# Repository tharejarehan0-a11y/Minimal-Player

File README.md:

# Minimal Player

**All the recordings are in JOURNAL.MD**

Minimal player is a device i can use to listen music in a compact way with only wired earphones offline and without worrying too much about the battery as it has a long battery life

---

## Why I Created This

The inspiration was from the need of having something i can carry everyday with me and listen music from with looking asthetic at the same times and some device with which i can use my wired earphones. But the thing is that i like to use such a device that gives only audio output through the audio jack bcz when you unplug it . It suddenly starts to play and doesnt stop i like that env where i can listen to music and no one disturbs me that is who i am and who i always will be . So i though why not create an Mp3 player where it has cool aesthetic design and also fulfills my requirements so i started with a simple pcb and then i came upon dac onto that and the battery mangagement we will talk more about that later . but for now i then did the routing and created the case the case was also quite complicated which we will cover on how to create that in aa nutshell in the next segment.

---

## How to create the MP3 schematics

I started by taking the raspberry pi pico cause it is the most easiest to work with microboard and also one of the most powerful ones also one more thing that attracted me about it was that it is micropython based which made the mechanics of code really easy for me to be done in the board itself. Then i came up with the decoupling of it and a switch for booting and stuff and then i stranded upon the micro sd slot the micro slot was a great option because it is one of the easiest to work with and works with the UART protocol which makes the wirinig also quite easy . Then i came upto the question okay i stored the data i have a microboard but what will i do of js the data the data also needs to play and what will play that that is the DAC and then i added the DAC to the MP3 Player which was quite complicated tho but still i added that and . It was a very difficult task to choose the right one for me , I Chose the PCM5102A for this and did stuff . I then continued to add the audio jack to it because the signals need to convert to sound somehow and i need my quite env after that i continued with working with the battery management and added the batter connector and the usb c for charging i also added the voltage regulator for stuff that requires 3.3v and 5v and handeled both separately and then i added some switches and lights for basic controls and also basic checks and then i chose to start with the rotatory encoders for more controls and then i switched to the pcb

---

## PCB

The pcb was quite complicated tho ngl I had to take care that the digital and analog signals do not interfare each other and also i have to take care of the thickness of the routing at different position due to the power management system itself and different power requiremwents here and there and then i went onto vias and stuff and it was quite a fast task tho 

---

## Case

Then i went onto the case and stuff . I wanted a quite aesthetic case tbh but at the same time I also wanted a case that fits my requirements like to be minimal and to signify that i am in my zone but still cool so i went with the orange and white color theme i know sounds a bit off but seems to fit my thingy and then what i did was i added little engravings at the sides of the case and added rotatory encoders to it i added two of them because i wanted to control the audio with one whereas the soong qeue with the other was quite a complicated task to add and make the cover for the rotatory encoders.

---

## Bill of Materials (BOM)

The table below lists all components used in the Minimal Player, matching the exact footprints and values from the KiCad PCB design layout. 

| Designator | Value | Footprint | Qty | India Sourcing / Purchase Links |
| :--- | :--- | :--- | :--- | :--- |
| **A1** | RaspberryPi_Pico | RaspberryPi_Pico_Common_THT | 1 | [Robu.in - Raspberry Pi Pico](https://robu.in/product/raspberry-pi-pico/) |
| **BT1** | Battery Connector | JST_PH_B2B-PH-K_1x02_P2.00mm_Vertical | 1 | [Robu.in - JST PH 2.0mm Male Header](https://robu.in/product/jst-ph-2-0-2-pin-male-connector-straight/) |
| **C1, C10, C11, C14, C15, C3** | $10\,\mu\text{F}$ | 0805 SMD Capacitor | 6 | [ElectronicsComp - 10uF 0805 Ceramic](https://www.electronicscomp.com/10uf-25v-0805-smd-capacitor) |
| **C12** | $2.2\text{ nF}$ | 0805 SMD Capacitor | 1 | [ElectronicsComp - 2.2nF 0805 Ceramic](https://www.electronicscomp.com/2.2nf-50v-0805-smd-capacitor) |
| **C13, R13** | 470 *(See Notes)* | 0805 SMD | 2 | [Resistor (470 $\Omega$)](https://www.electronicscomp.com/470-ohm-0805-smd-resistor) / [Capacitor (470 pF)](https://www.electronicscomp.com/470pf-50v-0805-smd-capacitor) |
| **C2, C5, C6, C8, C9** | $0.1\,\mu\text{F}$ | 0805 SMD Capacitor | 5 | [ElectronicsComp - 0.1uF 0805 Ceramic](https://www.electronicscomp.com/0.1uf-50v-0805-smd-capacitor) |
| **C4, C7** | $2.2\,\mu\text{F}$ | 0805 SMD Capacitor | 2 | [ElectronicsComp - 2.2uF 0805 Ceramic](https://www.electronicscomp.com/2.2uf-50v-0805-smd-capacitor) |
| **D1, D2** | LED_Small | 0805 SMD LED | 2 | [Robu.in - 0805 SMD LED Kit](https://robu.in/product/0805-smd-led-diode-assortment-kit-5-colors/) |
| **J1** | USB_C_Receptacle_14P | USB_C_Receptacle_HRO_TYPE-C-31-M-12 | 1 | [Robu.in - TYPE-C-31-M-12 Compatible 16P SMT](https://robu.in/product/usb-c-type-c-female-connector-16-pin-surface-mount/) |
| **J2** | Micro_SD_Card Slot | microSD_HC_Molex_104031-0811 | 1 | [ElectronicsComp - Push-Push MicroSD Slot](https://www.electronicscomp.com/micro-sd-card-slot-socket-smd-push-push-type) / [DigiKey India - Molex Exact](https://www.digikey.in/en/products/detail/molex/1040310811/3044122) |
| **J3** | AudioJack3 | Jack_3.5mm_CUI_SJ1-3523N_Horizontal | 1 | [DigiKey India - CUI SJ1-3523N Exact](https://www.digikey.in/en/products/detail/cui-devices/SJ1-3523N/738686) |
| **R1, R11, R2** | $5.1\text{ k}\Omega$ | 0805 SMD Resistor | 3 | [ElectronicsComp - 5.1k 0805 Resistor](https://www.electronicscomp.com/5.1k-ohm-0805-smd-resistor) |
| **R10** | $1.2\text{ k}\Omega$ | 0805 SMD Resistor | 1 | [ElectronicsComp - 1.2k 0805 Resistor](https://www.electronicscomp.com/1.2k-ohm-0805-smd-resistor) |
| **R12, R14, R5, R6, R7, R8, TH1** | $10\text{ k}\Omega$ *(See Notes)* | 0805 SMD | 7 | [Resistor (10k $\Omega$)](https://www.electronicscomp.com/10k-ohm-0805-smd-resistor) / [NTC Thermistor](https://www.electronicscomp.com/10k-ntc-thermistor-smd-0805) |
| **R3, R4** | $1\text{ k}\Omega$ | 0805 SMD Resistor | 2 | [ElectronicsComp - 1k 0805 Resistor](https://www.electronicscomp.com/1k-ohm-0805-smd-resistor) |
| **R9** | 0.4 / 400 $\Omega$ | 0805 SMD Resistor | 1 | [ElectronicsComp - 0805 SMD Resistor Assortment](https://www.electronicscomp.com/0805-smd-resistor-kit-36-values) |
| **SW1, SW2, SW3, SW4** | SW_SPST | SW_PUSH_6mm_H4.3mm | 4 | [Robu.in - 6x6x4.3mm Tactile Switch](https://robu.in/product/6x6x4-3mm-tactile-micro-push-button-switch-2-pin/) |
| **SW5** | RotaryEncoder | RotaryEncoder_Bourns_Vertical_PEC12R | 1 | [ElectronicsComp - EC11/12 with Switch](https://www.electronicscomp.com/ec11-rotary-encoder-with-switch-20mm-half-shaft) / [DigiKey India - Bourns Exact](https://www.digikey.in/en/products/detail/bourns-inc/PEC12R-4220F-S0024/3780188) |
| **U1** | TP4056-42-ESOP8 | SOIC-8-1EP (Exposed Thermal Pad) | 1 | [ElectronicsComp - TP4056 IC](https://www.electronicscomp.com/tp4056-linear-li-ion-battery-charger-ic) |
| **U2** | PCM5102A | TSSOP-20_4.4x6.5mm_P0.65mm | 1 | [ElectronicsComp - PCM5102A IC](https://www.electronicscomp.com/pcm5102a-audio-dac-ic-tssop-20) / [DigiKey India - TI Original](https://www.digikey.in/en/products/detail/texas-instruments/PCM5102APWR/3055979) |

---

# Schematics with Picture

The schematics were not that difficult because both the newer components had the datasheets to be followed the TP4056A and the PAM DAC they were easy to setup but the newer things that i explored onto this project were the electrolytic capcitors and how they have more capacitors and i also learned about this like analog and digital signals are different but sometimes when you have a project where you are going whith a pcb design for only 2 layers you can have same ground for both of them so i had the same ground for both of them and the TP4056 helped a lot with having a stable current towards the pico so that it can run easily and at last the PAM is a machine when it comes to audio only via headphones and works with the 3 pin audio jack that i setted up. I also added rotatory encoder , the buttons and a micro sd card a usb c and a lithium battery which can be recharged 

<br>

# PCB with picture

Then I started with the PCB it was really the hard part to deal with. I started by placing all the components but there were like so many capacitors and resistors that were to be placed which made it so confusing to set it up . So I took the schematics as the reference and placed all the capacitors as it was in that and then I started with routing it and got to know that the traces with the power are to be kept thick and the digital can be thin so i did it all wrong at the first try but got it on the second try. Then was the time to fix the errors . I had like so many errors I had to deal with so i started with the short errors all the way to body malformed errors and stuff and did that at last by filling the zone with AGND as the net 

<br>

# CAD with picture

Onshape is the best . I started by drawing two rectangles and then i extruded the part that was common to only one bigger rectangle in which with the same center was the other rectange and then i extruded it then i made the sketched for those tiny rectangular holes onto the sides of it and with the help of linear pattern i redrew them all easily and then i removed them from the sides to a certain extent to give a retro vibe then i imported the step file for the pcb and then what I did was i made the lower case and the upper case derived some parts and sketches drew the rotatory encoder the buttons . Imported the step files for the springs and the battery and then made the assembly that was it in all 
Onshape link : https://cad.onshape.com/documents/f82830b6c3d912c29ecf4908/w/00f5a3130b75aa3be964c3b3/e/6c625d5a5e73e1ecfabf8af3?renderMode=0&uiState=6a2fab96a442fa85ac58667a

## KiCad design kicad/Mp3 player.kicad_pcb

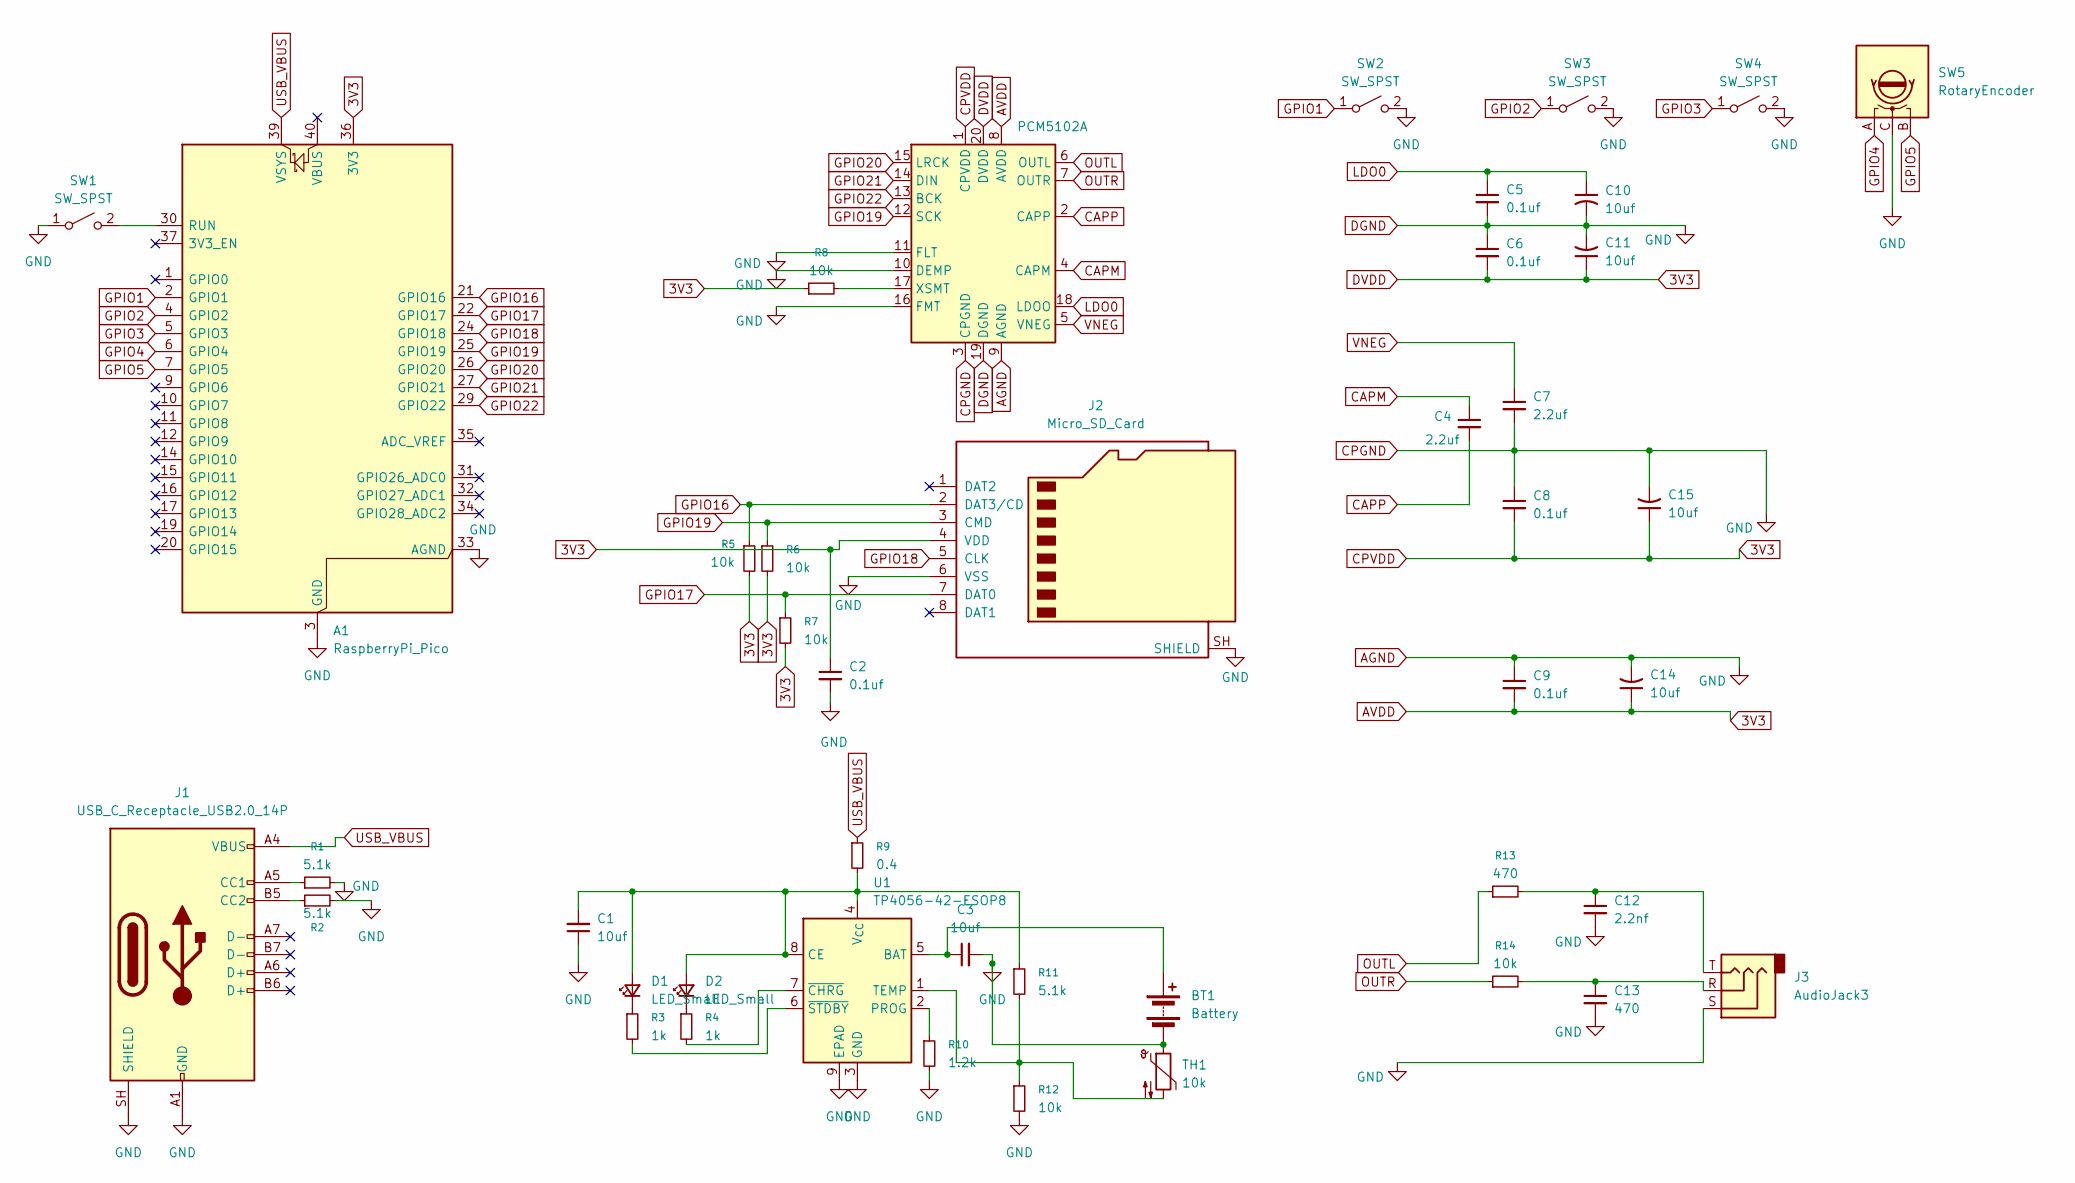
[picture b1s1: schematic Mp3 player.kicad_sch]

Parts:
A1: RaspberryPi_Pico; RaspberryPi_Pico_Common_THT
BT1: Battery; JST_PH_B2B-PH-K_1x02_P2.00mm_Vertical
C1, C3, C10, C11, C14, C15: 10uf; C_0805_2012Metric
C2, C5, C6, C8, C9: 0.1uf; C_0805_2012Metric
C4, C7: 2.2uf; C_0805_2012Metric
C12: 2.2nf; C_0805_2012Metric_Pad1.18x1.45mm_HandSolder
C13: 470; R_0805_2012Metric
D1, D2: LED_Small; LED_0805_2012Metric
J1: USB_C_Receptacle_USB2.0_14P; USB_C_Receptacle_HRO_TYPE-C-31-M-12
J2: Micro_SD_Card; microSD_HC_Molex_104031-0811
J3: AudioJack3; Jack_3.5mm_CUI_SJ1-3523N_Horizontal
R1, R2, R11: 5.1k; R_0805_2012Metric
R3, R4: 1k; R_0805_2012Metric
R5, R6, R7, R8, R12, R14: 10k; R_0805_2012Metric
R9: 0.4; R_0805_2012Metric
R10: 1.2k; R_0805_2012Metric
R13: 470; R_0805_2012Metric
SW1, SW2, SW3, SW4: SW_SPST; SW_PUSH_6mm_H4.3mm
SW5: RotaryEncoder; RotaryEncoder_Bourns_Vertical_PEC12R-3x17F-Nxxxx
TH1: 10k; R_0805_2012Metric
U1: TP4056-42-ESOP8; SOIC-8-1EP_3.9x4.9mm_P1.27mm_EP2.41x3.3mm_ThermalVias
U2: PCM5102A; TSSOP-20_4.4x6.5mm_P0.65mm

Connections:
3V3: A1.36 (3V3), C2.1, C6.2, C8.2, C9.2, C11.1, C14.1, C15.1, J2.4 (VDD), R5.2, R6.2, R7.2, R8.1, U2.1 (CPVDD), U2.8 (AVDD), U2.20 (DVDD)
AGND: A1.3 (GND), A1.8 (GND), A1.13 (GND), A1.18 (GND), A1.23 (GND), A1.28 (GND), A1.33 (AGND), A1.38 (GND), BT1.2 (-), C1.1, C2.2, C3.2, C5.2, C6.1, C7.2, C8.1, C9.1, C10.2, C11.2, C12.2, C13.2, C14.2, C15.2, J1.A1 (GND), J1.A12 (GND), J1.B1 (GND), J1.B12 (GND), J1.SH (SHIELD), J2.6 (VSS), J2.SH (SHIELD), J3.S, R1.2, R2.2, R10.2, R12.2, SW1.1 (A), SW2.2 (B), SW3.2 (B), SW4.2 (B), SW5.C, TH1.1, U1.3 (GND), U1.9 (EPAD), U2.3 (CPGND), U2.9 (AGND), U2.10 (DEMP), U2.11 (FLT), U2.16 (FMT), U2.19 (DGND)
CAPM: C4.1, U2.4 (CAPM)
CAPP: C4.2, U2.2 (CAPP)
GPIO1: A1.2 (GPIO1), SW2.1 (A)
GPIO2: A1.4 (GPIO2), SW3.1 (A)
GPIO3: A1.5 (GPIO3), SW4.1 (A)
GPIO4: A1.6 (GPIO4), SW5.A
GPIO5: A1.7 (GPIO5), SW5.B
GPIO16: A1.21 (GPIO16), J2.2 (DAT3/CD), R5.1
GPIO17: A1.22 (GPIO17), J2.7 (DAT0), R7.1
GPIO18: A1.24 (GPIO18), J2.5 (CLK)
GPIO19: A1.25 (GPIO19), J2.3 (CMD), R6.1, U2.12 (SCK)
GPIO20: A1.26 (GPIO20), U2.15 (LRCK)
GPIO21: A1.27 (GPIO21), U2.14 (DIN)
GPIO22: A1.29 (GPIO22), U2.13 (BCK)
LDO0: C5.1, C10.1, U2.18 (LDOO)
unnamed: A1.30 (RUN), SW1.2 (B)
unnamed: BT1.1 (+), C3.1, U1.5 (BAT)
unnamed: C12.1, J3.T, R13.2
unnamed: C13.1, J3.R, R14.2
unnamed: C1.2, D1.2 (A), D2.2 (A), R9.2, R11.1, U1.4 (V_{CC}), U1.8 (CE)
unnamed: D1.1 (K), R3.1
unnamed: D2.1 (K), R4.1
unnamed: J1.A5 (CC1), R1.1
unnamed: J1.B5 (CC2), R2.1
unnamed: R10.1, U1.2 (PROG)
unnamed: R11.2, R12.1, TH1.2, U1.1 (TEMP)
unnamed: R4.2, U1.7 (~CHRG)
unnamed: R3.2, U1.6 (~STDBY)
unnamed: R8.2, U2.17 (XSMT)
OUTL: R13.1, U2.6 (OUTL)
OUTR: R14.1, U2.7 (OUTR)
USB_VBUS: A1.39 (VSYS), J1.A4 (VBUS), J1.A9 (VBUS), J1.B4 (VBUS), J1.B9 (VBUS), R9.1
VNEG: C7.1, U2.5 (VNEG)

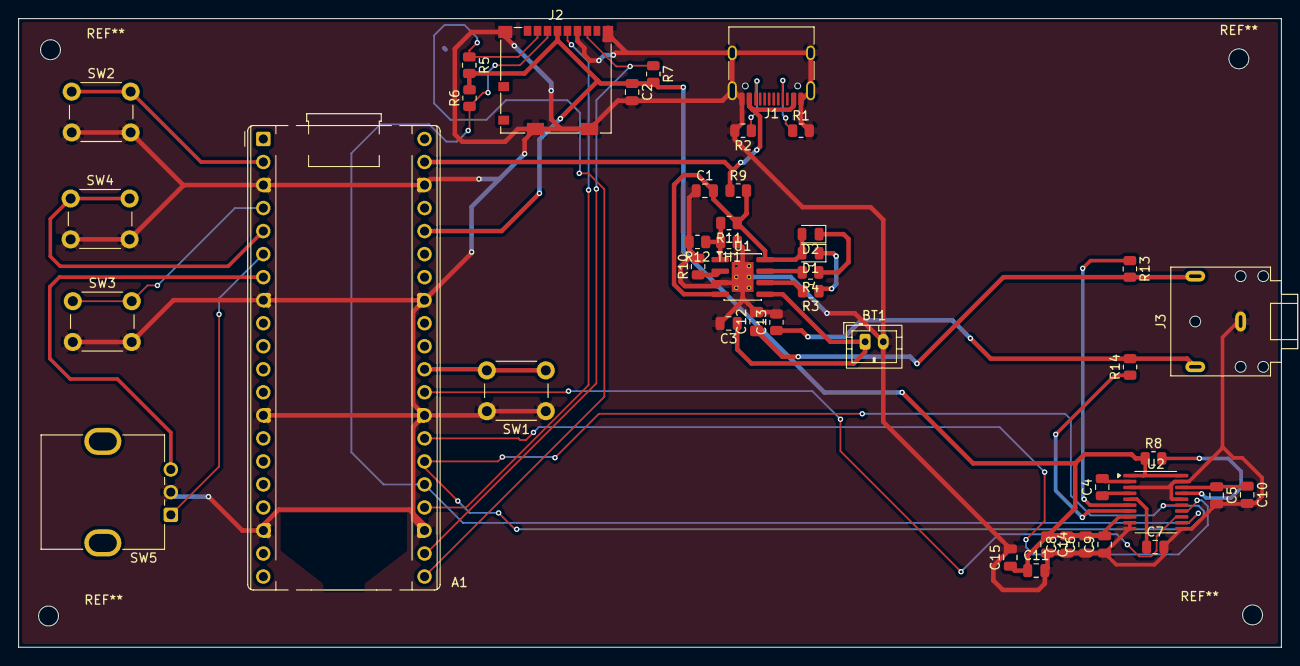
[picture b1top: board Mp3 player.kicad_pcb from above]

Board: 2 copper layers, 139.3 x 69.3 mm, 44 parts (0 on the bottom side), 35 nets.

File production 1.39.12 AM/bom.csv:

Designator,Footprint,Quantity,Value,LCSC Part #
A1,RaspberryPi_Pico_Common_THT,1,RaspberryPi_Pico,
BT1,JST_PH_B2B-PH-K_1x02_P2.00mm_Vertical,1,Battery,
"C1, C10, C11, C14, C15, C3",0805,6,10uf,
C12,0805,1,2.2nf,
"C13, R13",0805,2,470,
"C2, C5, C6, C8, C9",0805,5,0.1uf,
"C4, C7",0805,2,2.2uf,
"D1, D2",0805,2,LED_Small,
J1,USB_C_Receptacle_HRO_TYPE-C-31-M-12,1,USB_C_Receptacle_USB2.0_14P,
J2,microSD_HC_Molex_104031-0811,1,Micro_SD_Card,
J3,Jack_3.5mm_CUI_SJ1-3523N_Horizontal,1,AudioJack3,
"R1, R11, R2",0805,3,5.1k,
R10,0805,1,1.2k,
"R12, R14, R5, R6, R7, R8, TH1",0805,7,10k,
"R3, R4",0805,2,1k,
R9,0805,1,0.4,
"SW1, SW2, SW3, SW4",SW_PUSH_6mm_H4.3mm,4,SW_SPST,
SW5,RotaryEncoder_Bourns_Vertical_PEC12R-3x17F-Nxxxx,1,RotaryEncoder,
U1,SOIC-8-1EP_3.9x4.9mm_P1.27mm_EP2.41x3.3mm_ThermalVias,1,TP4056-42-ESOP8,
U2,TSSOP-20_4.4x6.5mm_P0.65mm,1,PCM5102A,

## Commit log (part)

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2026-06-14 Enhance README with project details and specifications
    Expanded the README to include details about the Minimal Player's purpose, inspiration, bill of materials, and hardware features.
2026-06-14 upload of all the components
2026-06-14 Update README with image for visual enhancement
    Added an image to enhance the README presentation.
2026-06-14 did with the req
2026-06-15 firmware
2026-06-15 Enhance README with project details and images
    Expanded the README with detailed sections on schematics, PCB design, and CAD process, including images and explanations of the components used and challenges faced.
2026-06-15 Revise BOM with detailed component information
    Updated the Bill of Materials (BOM) section with detailed component references, descriptions, quantities, and purchase links.
2026-06-15 Update CAD section with project details and link
    Added Onshape link and expanded CAD project description.
2026-06-24 Revise README to clarify Minimal Player features
    Updated the README to reflect the purpose and inspiration behind the Minimal Player, emphasizing its compact design and functionality.
2026-06-24 Remove hardware features section from README
    Removed hardware features and design choices section from README.
2026-06-24 Update Raspberry Pi Pico sourcing links in README
    Removed one of the purchase links for Raspberry Pi Pico.
